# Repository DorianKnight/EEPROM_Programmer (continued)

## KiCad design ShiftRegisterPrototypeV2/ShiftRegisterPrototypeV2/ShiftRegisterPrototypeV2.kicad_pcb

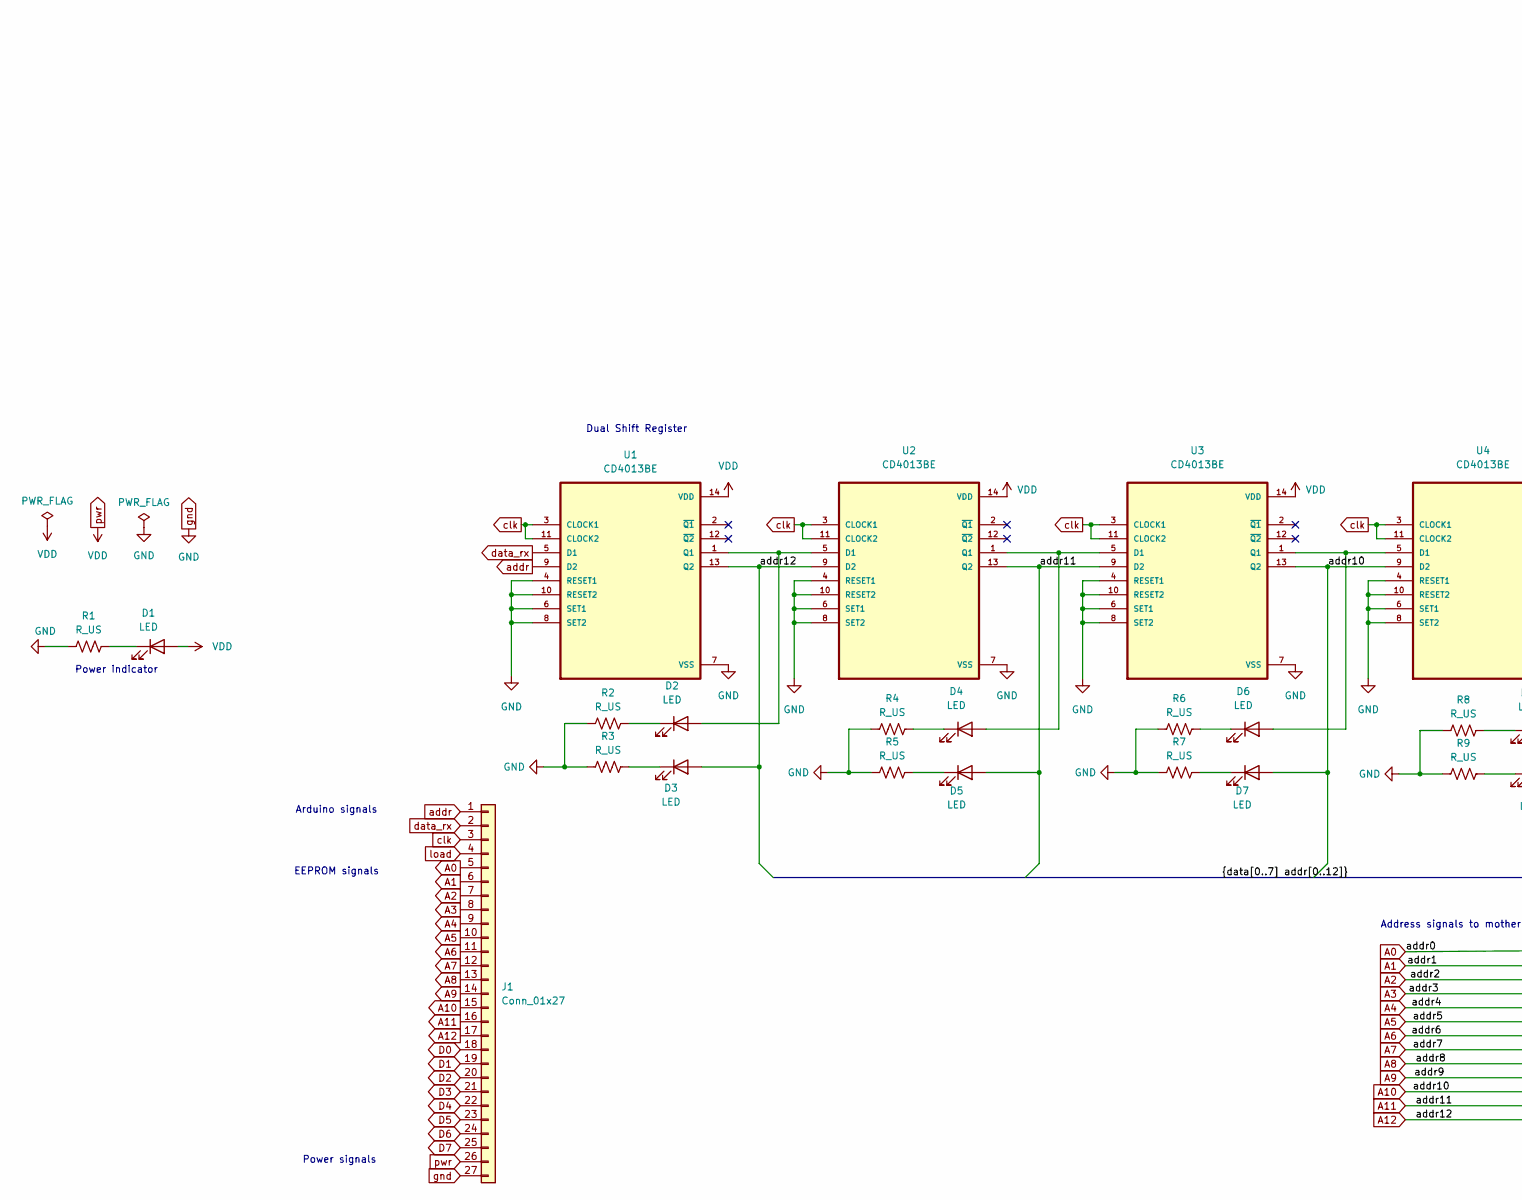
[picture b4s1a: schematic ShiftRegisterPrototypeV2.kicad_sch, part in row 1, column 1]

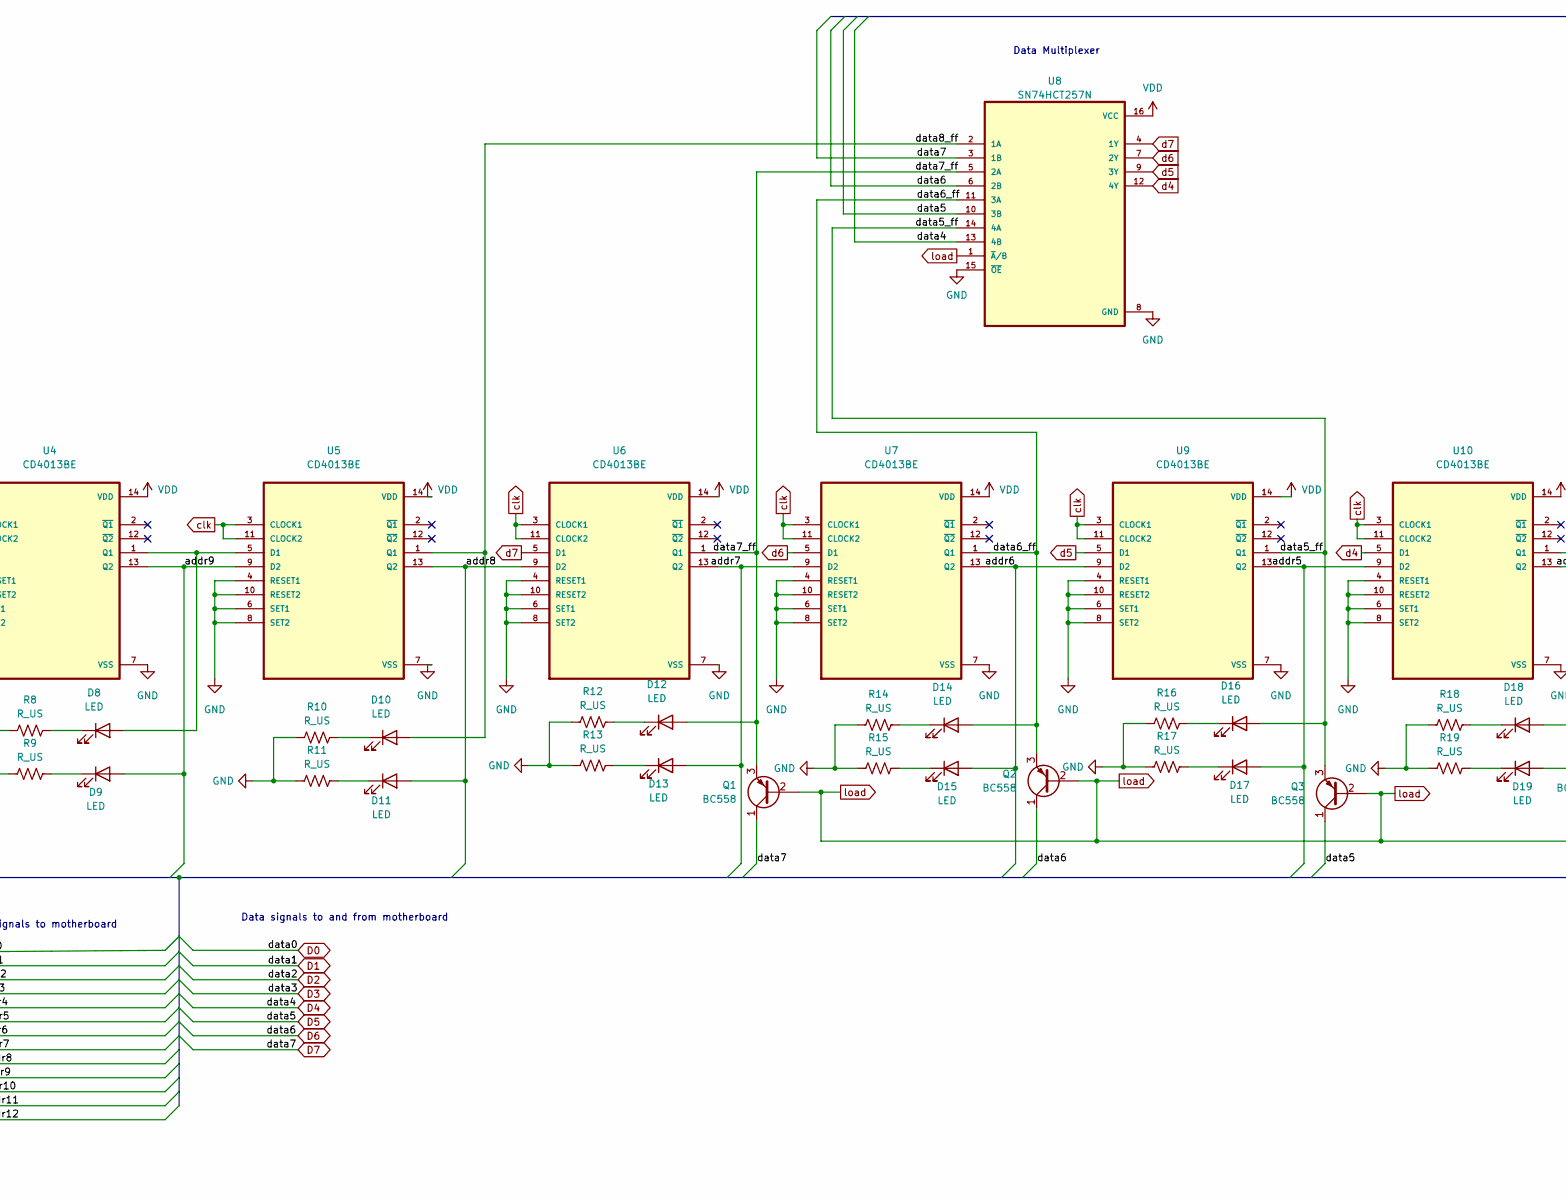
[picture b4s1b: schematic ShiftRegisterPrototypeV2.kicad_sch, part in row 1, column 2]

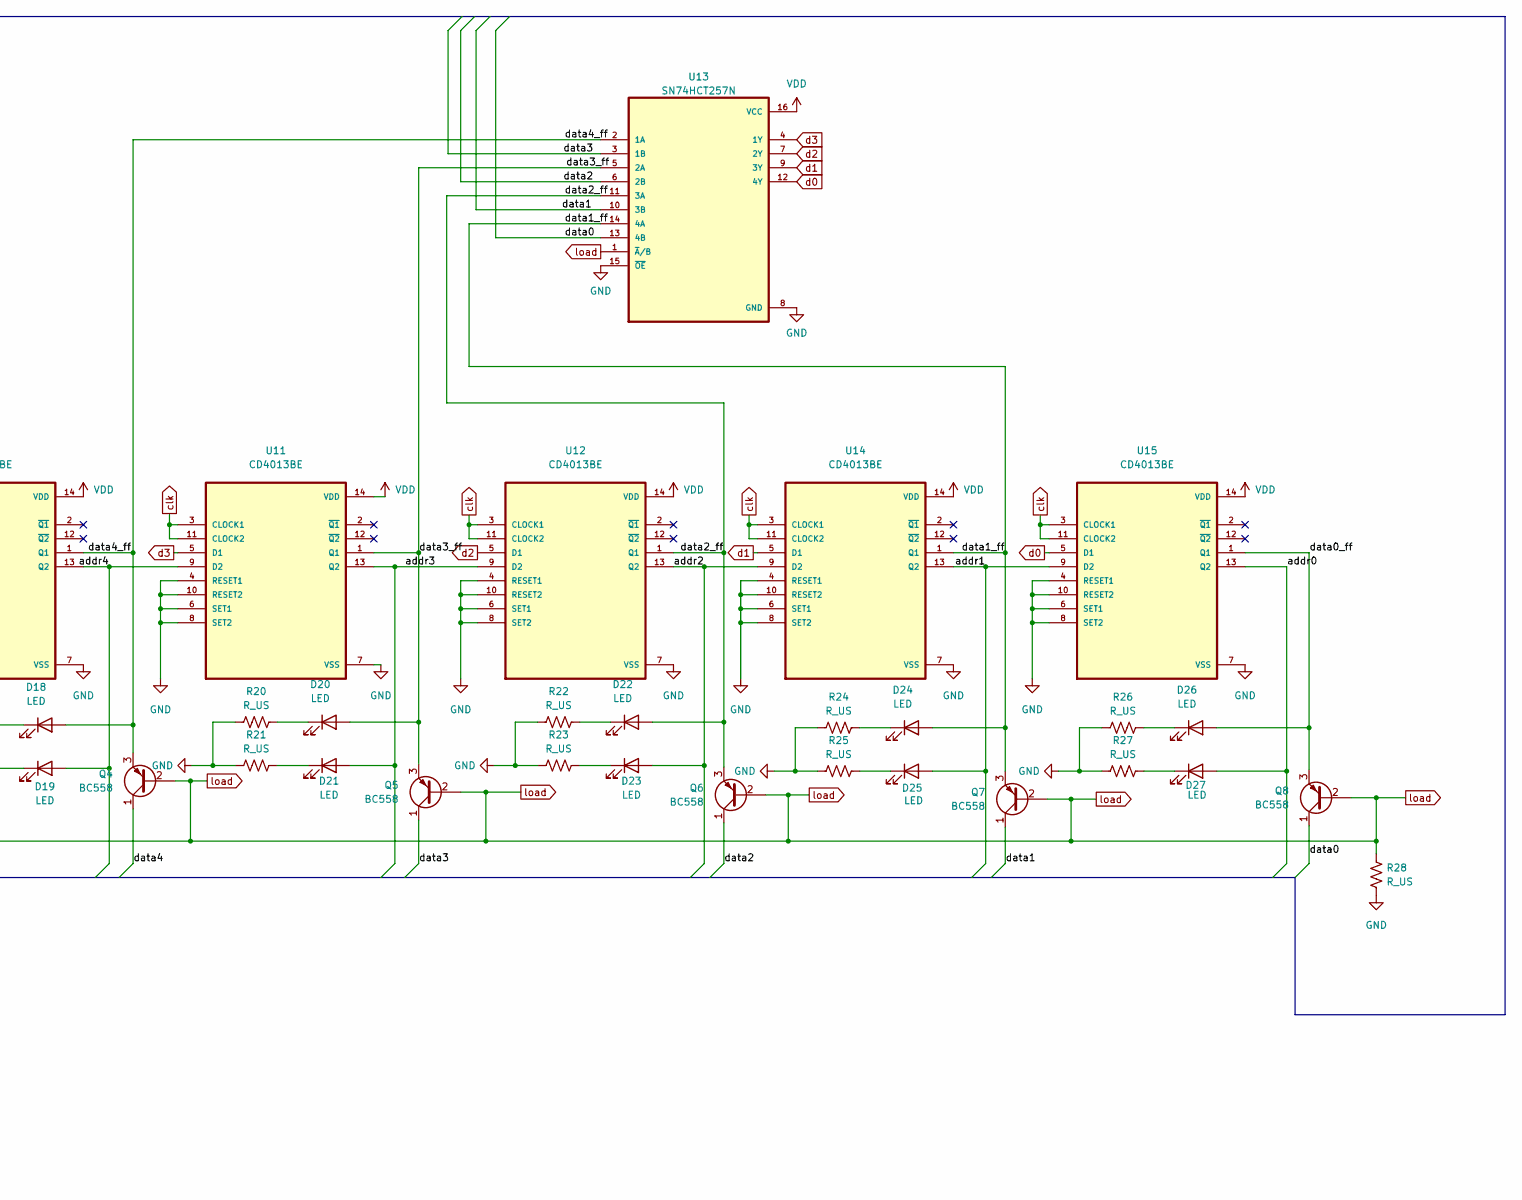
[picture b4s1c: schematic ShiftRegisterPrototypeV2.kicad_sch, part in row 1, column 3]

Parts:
D1: LED; LED_D3.0mm_white
D2, D4, D6, D8, D10, D12, D14, D16, D18, D20, D22, D24, D26: LED; LED_D3.0mm_red
D3, D5, D7, D9, D11, D13, D15, D17, D19, D21, D23, D25, D27: LED; LED_D3.0mm_green
J1: Conn_01x27; PinHeader_1x27_P2.54mm_Horizontal
Q1, Q2, Q3, Q4, Q5, Q6, Q7, Q8: BC558; TO-92_Inline
R1, R2, R3, R4, R5, R6, R7, R8, R9, R10, R11, R12, R13, R14, R15, R16, R17, R18, R19, R20, R21, R22, R23, R24, R25, R26, R27, R28: R_US; R_Axial_DIN0204_L3.6mm_D1.6mm_P5.08mm_Horizontal
U1, U2, U3, U4, U5, U6, U7, U9, U10, U11, U12, U14, U15: CD4013BE; DIP794W45P254L1969H508Q14
U8, U13: SN74HCT257N; DIP794W45P254L1969H508Q16

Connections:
/data0_ff: D26.2 (A), Q8.3 (E), U15.1 (Q1)
/data1_ff: D24.2 (A), Q7.3 (E), U13.14 (4A), U14.1 (Q1)
/data2_ff: D22.2 (A), Q6.3 (E), U12.1 (Q1), U13.11 (3A)
/data3_ff: D20.2 (A), Q5.3 (E), U11.1 (Q1), U13.5 (2A)
/data4_ff: D18.2 (A), Q4.3 (E), U10.1 (Q1), U13.2 (1A)
/data5_ff: D16.2 (A), Q3.3 (E), U8.14 (4A), U9.1 (Q1)
/data6_ff: D14.2 (A), Q2.3 (E), U7.1 (Q1), U8.11 (3A)
/data7_ff: D12.2 (A), Q1.3 (E), U6.1 (Q1), U8.5 (2A)
/data8_ff: D10.2 (A), U5.1 (Q1), U8.2 (1A)
A0: D27.2 (A), J1.5, U15.13 (Q2)
A1: D25.2 (A), J1.6, U14.13 (Q2), U15.9 (D2)
A2: D23.2 (A), J1.7, U12.13 (Q2), U14.9 (D2)
A3: D21.2 (A), J1.8, U11.13 (Q2), U12.9 (D2)
A4: D19.2 (A), J1.9, U10.13 (Q2), U11.9 (D2)
A5: D17.2 (A), J1.10, U9.13 (Q2), U10.9 (D2)
A6: D15.2 (A), J1.11, U7.13 (Q2), U9.9 (D2)
A7: D13.2 (A), J1.12, U6.13 (Q2), U7.9 (D2)
A8: D11.2 (A), J1.13, U5.13 (Q2), U6.9 (D2)
A9: D9.2 (A), J1.14, U4.13 (Q2), U5.9 (D2)
A10: D7.2 (A), J1.15, U3.13 (Q2), U4.9 (D2)
A11: D5.2 (A), J1.16, U2.13 (Q2), U3.9 (D2)
A12: D3.2 (A), J1.17, U1.13 (Q2), U2.9 (D2)
D0: J1.18, Q8.1 (C), U13.13 (4B)
D1: J1.19, Q7.1 (C), U13.10 (3B)
D2: J1.20, Q6.1 (C), U13.6 (2B)
D3: J1.21, Q5.1 (C), U13.3 (1B)
D4: J1.22, Q4.1 (C), U8.13 (4B)
D5: J1.23, Q3.1 (C), U8.10 (3B)
D6: J1.24, Q2.1 (C), U8.6 (2B)
D7: J1.25, Q1.1 (C), U8.3 (1B)
unnamed: D1.1 (K), R1.2
unnamed: D2.1 (K), R2.2
unnamed: D2.2 (A), U1.1 (Q1), U2.5 (D1)
unnamed: D3.1 (K), R3.2
unnamed: D4.1 (K), R4.2
unnamed: D4.2 (A), U2.1 (Q1), U3.5 (D1)
unnamed: D5.1 (K), R5.2
unnamed: D6.1 (K), R6.2
unnamed: D6.2 (A), U3.1 (Q1), U4.5 (D1)
unnamed: D7.1 (K), R7.2
unnamed: D8.1 (K), R8.2
unnamed: D8.2 (A), U4.1 (Q1), U5.5 (D1)
unnamed: D9.1 (K), R9.2
unnamed: D10.1 (K), R10.2
unnamed: D11.1 (K), R11.2
unnamed: D12.1 (K), R12.2
unnamed: D13.1 (K), R13.2
unnamed: D14.1 (K), R14.2
unnamed: D15.1 (K), R15.2
unnamed: D16.1 (K), R16.2
unnamed: D17.1 (K), R17.2
unnamed: D18.1 (K), R18.2
unnamed: D19.1 (K), R19.2
unnamed: D20.1 (K), R20.2
unnamed: D21.1 (K), R21.2
unnamed: D22.1 (K), R22.2
unnamed: D23.1 (K), R23.2
unnamed: D24.1 (K), R24.2
unnamed: D25.1 (K), R25.2
unnamed: D26.1 (K), R26.2
unnamed: D27.1 (K), R27.2
addr: J1.1, U1.9 (D2)
clk: J1.3, U1.3 (CLOCK1), U1.11 (CLOCK2), U2.3 (CLOCK1), U2.11 (CLOCK2), U3.3 (CLOCK1), U3.11 (CLOCK2), U4.3 (CLOCK1), U4.11 (CLOCK2), U5.3 (CLOCK1), U5.11 (CLOCK2), U6.3 (CLOCK1), U6.11 (CLOCK2), U7.3 (CLOCK1), U7.11 (CLOCK2), U9.3 (CLOCK1), U9.11 (CLOCK2), U10.3 (CLOCK1), U10.11 (CLOCK2), U11.3 (CLOCK1), U11.11 (CLOCK2), U12.3 (CLOCK1), U12.11 (CLOCK2), U14.3 (CLOCK1), U14.11 (CLOCK2), U15.3 (CLOCK1), U15.11 (CLOCK2)
d0: U13.12 (4Y), U15.5 (D1)
d1: U13.9 (3Y), U14.5 (D1)
d2: U12.5 (D1), U13.7 (2Y)
d3: U11.5 (D1), U13.4 (1Y)
d4: U8.12 (4Y), U10.5 (D1)
d5: U8.9 (3Y), U9.5 (D1)
d6: U7.5 (D1), U8.7 (2Y)
d7: U6.5 (D1), U8.4 (1Y)
data_rx: J1.2, U1.5 (D1)
gnd: J1.27, R1.1, R2.1, R3.1, R4.1, R5.1, R6.1, R7.1, R8.1, R9.1, R10.1, R11.1, R12.1, R13.1, R14.1, R15.1, R16.1, R17.1, R18.1, R19.1, R20.1, R21.1, R22.1, R23.1, R24.1, R25.1, R26.1, R27.1, R28.2, U1.4 (RESET1), U1.6 (SET1), U1.7 (VSS), U1.8 (SET2), U1.10 (RESET2), U2.4 (RESET1), U2.6 (SET1), U2.7 (VSS), U2.8 (SET2), U2.10 (RESET2), U3.4 (RESET1), U3.6 (SET1), U3.7 (VSS), U3.8 (SET2), U3.10 (RESET2), U4.4 (RESET1), U4.6 (SET1), U4.7 (VSS), U4.8 (SET2), U4.10 (RESET2), U5.4 (RESET1), U5.6 (SET1), U5.7 (VSS), U5.8 (SET2), U5.10 (RESET2), U6.4 (RESET1), U6.6 (SET1), U6.7 (VSS), U6.8 (SET2), U6.10 (RESET2), U7.4 (RESET1), U7.6 (SET1), U7.7 (VSS), U7.8 (SET2), U7.10 (RESET2), U8.8 (GND), U8.15 (~OE), U9.4 (RESET1), U9.6 (SET1), U9.7 (VSS), U9.8 (SET2), U9.10 (RESET2), U10.4 (RESET1), U10.6 (SET1), U10.7 (VSS), U10.8 (SET2), U10.10 (RESET2), U11.4 (RESET1), U11.6 (SET1), U11.7 (VSS), U11.8 (SET2), U11.10 (RESET2), U12.4 (RESET1), U12.6 (SET1), U12.7 (VSS), U12.8 (SET2), U12.10 (RESET2), U13.8 (GND), U13.15 (~OE), U14.4 (RESET1), U14.6 (SET1), U14.7 (VSS), U14.8 (SET2), U14.10 (RESET2), U15.4 (RESET1), U15.6 (SET1), U15.7 (VSS), U15.8 (SET2), U15.10 (RESET2)
load: J1.4, Q1.2 (B), Q2.2 (B), Q3.2 (B), Q4.2 (B), Q5.2 (B), Q6.2 (B), Q7.2 (B), Q8.2 (B), R28.1, U8.1 (~A/B), U13.1 (~A/B)
pwr: D1.2 (A), J1.26, U1.14 (VDD), U2.14 (VDD), U3.14 (VDD), U4.14 (VDD), U5.14 (VDD), U6.14 (VDD), U7.14 (VDD), U8.16 (VCC), U9.14 (VDD), U10.14 (VDD), U11.14 (VDD), U12.14 (VDD), U13.16 (VCC), U14.14 (VDD), U15.14 (VDD)

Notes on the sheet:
Dual Shift Register
Data signals to and from motherboard
Data Multiplexer
Arduino signals
Address signals to motherboard
Power indicator
EEPROM signals
Power signals

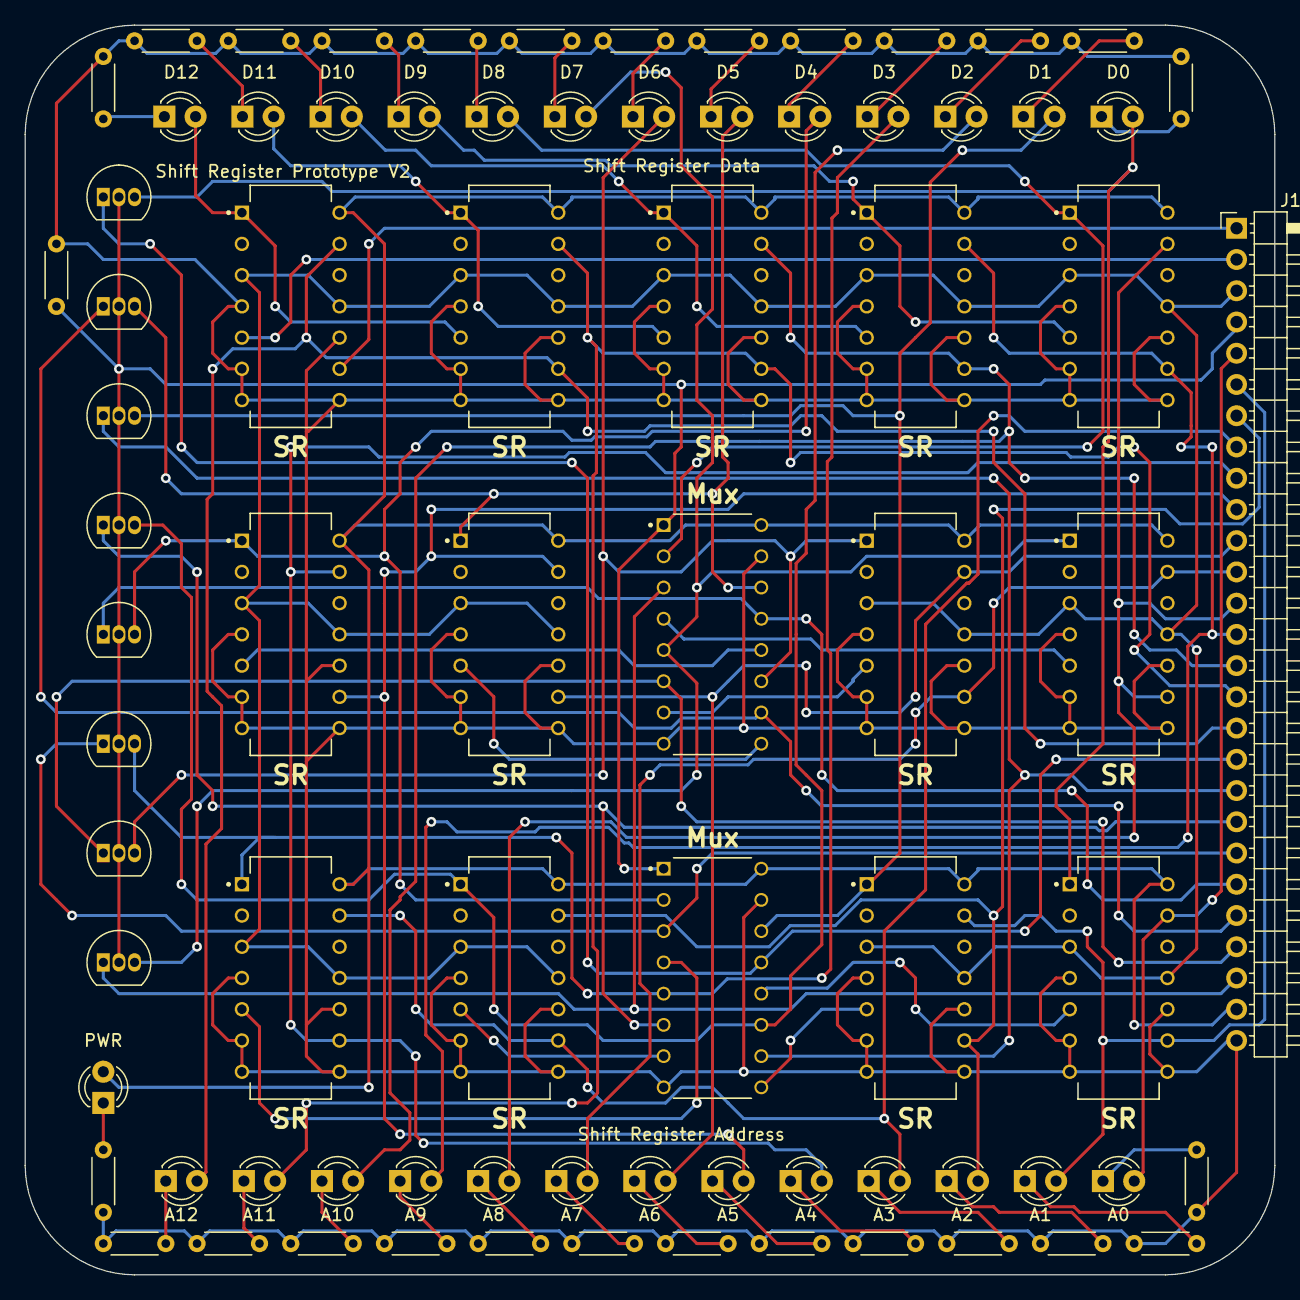
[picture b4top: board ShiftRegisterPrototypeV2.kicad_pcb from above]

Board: 2 copper layers, 101.6 x 101.6 mm, 79 parts (0 on the bottom side), 75 nets.

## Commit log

2025-06-29 Add EEPROM V2 PCB design
2025-06-29 Add current draft of documentation
2026-02-07 Add readme images
2026-02-07 Update high level user flow diagram
2026-02-07 Add Arduino driver code
